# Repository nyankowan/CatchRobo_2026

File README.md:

# CatchRobo_2026
キャチロボ2026で使用する回路データおよび複数マイコンのプログラムを一括管理するリポジトリ.
Team: OBT

## Directory structure
```text
CatchRobo_2026/
├── common/                     ESP32/STM32が共有するプラットフォーム非依存コード
│   ├── arm/
│   │   └── アームの物理パラメータ・ホーミング関連定数・出場チーム(ROBOT_TEAM)
│   │
│   ├── can_protocol/
│   │   └── CAN IDとデータフォーマットの対応定義
│   │
│   └── coordinate/
│       └── 直交座標・極座標変換
│
├── ESP32/
│   └── controller/
│       └── Main Controller(プロコン入力の受信とCANによる各STM32への指令)
│
├── STM32/
│   ├── common/
│   │   └── can/
│   │       └── STM32 HAL CANを使ったCAN送信のラッパー
│   │
│   ├── robomas_controller/
│   │   └── 両アームのr軸・deg軸(Robomaster)制御．ホーミング処理の中枢
│   │
│   ├── lower_arm_servo/
│   │   └── 下アームのハンド(Left/Middle/Right/Expand)とShaftサーボ制御
│   │
│   ├── upper_arm_servo/
│   │   └── 上アームのShaft/Zサーボ制御
│   │
│   └── assemble_servo/
│       └── 整理機構のサーボ制御
│
└── Kicad/
    ├── ESP/
    │   └── ESP Main Controller基板
    ├── STM32F303K8_lower_arm_servo/
    │   └── サーボ制御基板(lower_arm_servo/upper_arm_servo/assemble_servoで共用)
    ├── STM32F446RE_robomas_controller/
    │   └── ロボマス制御基板
    ├── servo/
    │   └── サーボ用補助基板
    └── library/
        └── 共通シンボル・フットプリント
```

各ディレクトリの詳細は，それぞれのREADMEを参照．

| ディレクトリ | README |
| :--- | :--- |
| 共有コード | [common/README.md](common/README.md) |
| CAN通信仕様 | [common/can_protocol/README.md](common/can_protocol/README.md) |
| Main Controller | [ESP32/controller/README.md](ESP32/controller/README.md) |
| STM32全体 | [STM32/README.md](STM32/README.md) |
| 部品リスト | [Kicad/README.md](Kicad/README.md) |

## Hardware

### Actuator
- Robomaster M3508
- DS3225 Servo

### Sensor
- リミットスイッチ(ホーミング用，robomas_controllerに接続)

### Communication
- CAN 1Mbps (ESP32 - STM32, STM32 - Robomaster)

CAN ID・データフォーマットの仕様は [common/can_protocol/README.md](common/can_protocol/README.md) を参照．

## System overview

```mermaid
graph LR
    Pad1[Gamepad1] <-->|Bluetooth| ESP32[ESP32<br>中央制御]
    Pad2[Gamepad2] <-->|Bluetooth| ESP32

    ESP32 --- CAN[CAN BUS]

    CAN --- STM1[STM32 #1<br>robomas_controller]
    CAN --- STM2[STM32 #2<br>lower_arm_servo]
    CAN --- STM3[STM32 #3<br>upper_arm_servo]
    CAN --- STM4[STM32 #4<br>assemble_servo]

    STM1 <-->|CAN| Motor[Robomaster Motor<br>M3508]
    Limit[リミットスイッチ] -->|GPIO| STM1
    STM2 -->|PWM| Servo1[DS3225<br>Left/Middle/Right/Expand/Shaft]
    STM3 -->|PWM| Servo2[DS3225<br>Shaft/Z]
    STM4 -->|PWM| Servo3[DS3225<br>Assemble]
```

## Development environment

### ESP32

#### Hardware
- ESP32-DevKitC-32E

#### Software
- ESP-IDF v5.5.4
- VS Code + ESP-IDF Extension

### STM32

#### Hardware
- STM32 NUCLEO-F303K8
- STM32 NUCLEO-F446RE

#### Software
- STM32CubeMX
- CMake
- VS Code + STM32CubeIDE Extension

### KiCad

#### Software
- KiCad 10.0

## Build

### ESP32

#### Setup
[ESP-IDF環境構築手順（Windows）](https://app.notion.com/p/Windows-36e23f78736380f7b838e187b781a125?v=2cd23f78736380928f93000c8fceebd6&source=copy_link)

[ESP-IDF環境構築手順（Linux）](https://app.notion.com/p/L-32323f7873638072bacfeb84175d09c4?v=2cd23f78736380928f93000c8fceebd6&source=copy_link)

#### Build
```bash
idf.py build
```
#### Flash
```bash
idf.py flash
```

### STM32

#### Setup
[Qiita: STM32の開発をVSCodeで行う](https://qiita.com/tanutanup/items/d680c92f5168fc3f0182) [@tanutanup(tanutanu p)様](https://qiita.com/tanutanup)

#### Build
各プロジェクト(`STM32/lower_arm_servo`, `STM32/upper_arm_servo`, `STM32/robomas_controller`, `STM32/assemble_servo`)のディレクトリで実行する．
```bash
cmake --preset Release
cmake --build --preset Release
```

## 出場チーム(ROBOT_TEAM)の設定

赤/青チームはフィールドが鏡合わせで，整理機構を左右逆側に取り付けるため，DEG軸のホーミング原点やShaftサーボの回転方向をチームごとに切り替える必要がある．

出場チームは `common/arm/inc/arm.h` の `ROBOT_TEAM`(`ROBOT_TEAM_RED` / `ROBOT_TEAM_BLUE`)としてビルド時の定数で持たせている．緊急停止スイッチでESP32/STM32が再起動しても値を保持する必要があるため，実行時に切り替える方式にはしていない．

**出場チームに応じて`arm.h`のこの値を書き換えた後は，`arm.h`を使う全ファームウェア(ESP32 Main Controller，STM32の`robomas_controller` / `lower_arm_servo` / `upper_arm_servo`)を必ずビルド・書き込みし直すこと．** 値がずれると，DEG軸のホーミングで検出するリミットスイッチと回転方向が基板間で食い違い，可動域の反対側の固定端に衝突する恐れがある．

詳細は [STM32/robomas_controller/README.md](STM32/robomas_controller/README.md) を参照．

## CI

`.github/workflows/` でpush/pull request時に全ファームウェアのビルドを確認している．

| Workflow | 内容 |
| :--- | :--- |
| `esp32-build.yml` | `ESP32/controller` をESP-IDF v5.5.4でビルド |
| `stm32-build.yml` | STM32の4プロジェクトを`cmake --preset Release`でビルド |

ESP-IDFのバージョンとSTM32のツールチェーンは，上記「Development environment」およびDev Containerの設定と揃えること．

## Dev Container (Docker)

ESP-IDF拡張とSTM32系拡張は同じVS Codeウィンドウで有効になっていると干渉するため，用途別にDev Container(Docker)を分けている．必要な拡張機能だけがコンテナ内にインストールされるので，都度手動で拡張をオン/オフする必要がない．

| フォルダを開く | 使うコンテナ | 有効になる拡張 |
| :--- | :--- | :--- |
| `ESP32/controller` | `ESP32/controller/.devcontainer` | ESP-IDF |
| `STM32` | `STM32/.devcontainer` | clangd, CMake Tools, Cortex-Debug |

使い方: 対象のフォルダ(リポジトリ全体ではなく上表のフォルダ)を`File > Open Folder...`で開き，コマンドパレットから`Dev Containers: Reopen in Container`を実行する．どちらのコンテナも各プロジェクトが参照する`common/`(リポジトリ直下)を含むリポジトリ全体をマウントしたうえで，開いたフォルダをエディタ上のワークスペースフォルダとして表示する．

`STM32/.devcontainer`は`lower_arm_servo`/`upper_arm_servo`/`robomas_controller`/`assemble_servo`の4プロジェクト共通で，どのプロジェクトも同じコンテナ内でビルドできる(各プロジェクトのディレクトリに`cd`して上記の`cmake --preset`コマンドを実行)．

`ESP32/controller/.devcontainer`はコンテナ作成時に`components/procon`が依存するBluepad32/BTstack(`~/.espressif/bluepad32`)を自動で取得する(`esp32-build.yml`と同じ手順)．取得結果はDockerボリュームにキャッシュされるため，コンテナを再作成しても毎回cloneし直すことはない．

ST-Link/シリアルポート経由でのフラッシュ・デバッグにはUSBデバイスをコンテナに渡す必要があり，Linuxホスト以外(Windows/macOS)では別途パススルー設定が必要な場合がある．

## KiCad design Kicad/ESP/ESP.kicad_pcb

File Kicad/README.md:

# Kicad

キャチロボ2026で使用する回路データ(KiCad 10.0)と，その部品リスト．

## Directory structure

```text
Kicad/
├── ESP/
│   └── ESP Main Controller基板(ESP32-DevKitC-32E)
│
├── STM32F303K8_lower_arm_servo/
│   └── サーボ制御基板(lower_arm_servo/upper_arm_servo/assemble_servoで共用)
│
├── STM32F446RE_robomas_controller/
│   └── ロボマス制御基板(NUCLEO-F446RE)
│
├── servo/
│   └── サーボ用補助基板
│
└── library/
    └── 共通シンボル・フットプリント
```

各基板に対応するファームウェアは [STM32/README.md](../STM32/README.md) および [ESP32/controller/README.md](../ESP32/controller/README.md) を参照．

## 部品リスト

このディレクトリにあるキャチロボ2026に向けて作った回路データのほかにも，
岡ロボで使われるCANトランシーバー回路も使用している．

### 回路基板実装部品
#### マイコン基板
- lower_arm_servo基板×3（上側アームと整理機構の制御基板に流用）     
以下一つあたりの部品
    - nucleo-f303k8
    - 3φLED×1
    - 470Ω抵抗×1
    - 5ピンソケット×1
    - 6ピンソケット×1
    - 15pin socket×2

- robomas_controller基板×1
    - nucleo-f446re
    - 19*2ピンソケット×2
    - hirose 2pin(DF1EC-2P-2.5DSA(35))×7
    - 5ピンソケット×2
    - 300Ω抵抗×1
    - φ3LED×1

- ESP Main controller基板×1
    - ESP32-DevKitC-32E
    - 19ピンソケット×2
    - 2ピンソケット×2
    - 5ピンソケット×1
    - φ3LED×7
    - 470Ω抵抗×7

#### 電源基板(N先輩制作)
- catchrobo_2026電源回路×1
    - リレー(942H-2C-24DS)×1
    - ヒューズ×3
    - 470μF×3
    - xt30オス×5
    - xt30メス×4
    - φ5LED×3
    - {1200, 330}Ω抵抗×3
- catchrobo_2026分電回路×2
    - 470μF×1
    - φ5LED×1
    - {1200, 330}Ω抵抗×1
    - xt30メス×4
    - xt30オス×1

#### 補助基板
- servo基板×3   
一つあたりの部品
    - 基板取付用XT30オス(XT30PW-M)×1
    - 1kΩ抵抗×1
    - 220Ω抵抗×5
    - φ3LED×1
    - 1000μF(50PX1000MEFC12.5X25)×1
    - 0.1μF(積層セラミックコンデンサー 0.1μF100V X7R 5mmピッチ)
    - 折れ6pin hirose (DF1E-6P-2.5DS(35))×1
    - 3ピンソケット×5（ヘッダでも可）

- canトランシーバ基板ver1.b×2
- canトランシーバ基板ver1.0×1
- canトランシーバ基板ver1.0 終端抵抗なし×3

- 6.6V -> 5V DCDCコンバータ×1
    - xt30オス×1
    - xt30メス×1

### コード類
#### 電源線
- 電源供給用micro-B×3（2m級×2）
- 電源供給用micro-B×1 （もしくは 2pin オスxt30メス×1）
- 電源供給用mini-B×1　（もしくは 2pin オスxt30メス×1）
- ロボマス電源延長用 xt30 オスメス ×4（15cm程度）
- xt30延長ケーブル×∞

#### 信号線
- リミットスイッチ 2pin hirose オス×6（2m級）
- マイコン間canbus接続用2pin hirose オスオス×4（2m級）
- サーボ電源供給用 xt30オスメス×3（2m級）
- ロボマスcan延長用 2pin hirose オスメス×4（15cm程度）
- canトランシーバ接続用6pinオスメスコネクタ×1（1pin NC）

#### その他
- サーボ延長用 3pin オスメス×5

### 非常停止ボタン　動作ランプなど
- プッシュロック・ターンリセットスイッチ×1
- φ20以上緑LED×1(HWシリーズ パイロットライトΦ22(突形 LED))
- 22VLipo×3
    - xt60オス - xt30メス変換ケーブル×1
- 6.6VLipo×1(並列につなぐ場合×2)
    - xt60オス - xt30メス変換ケーブル×1

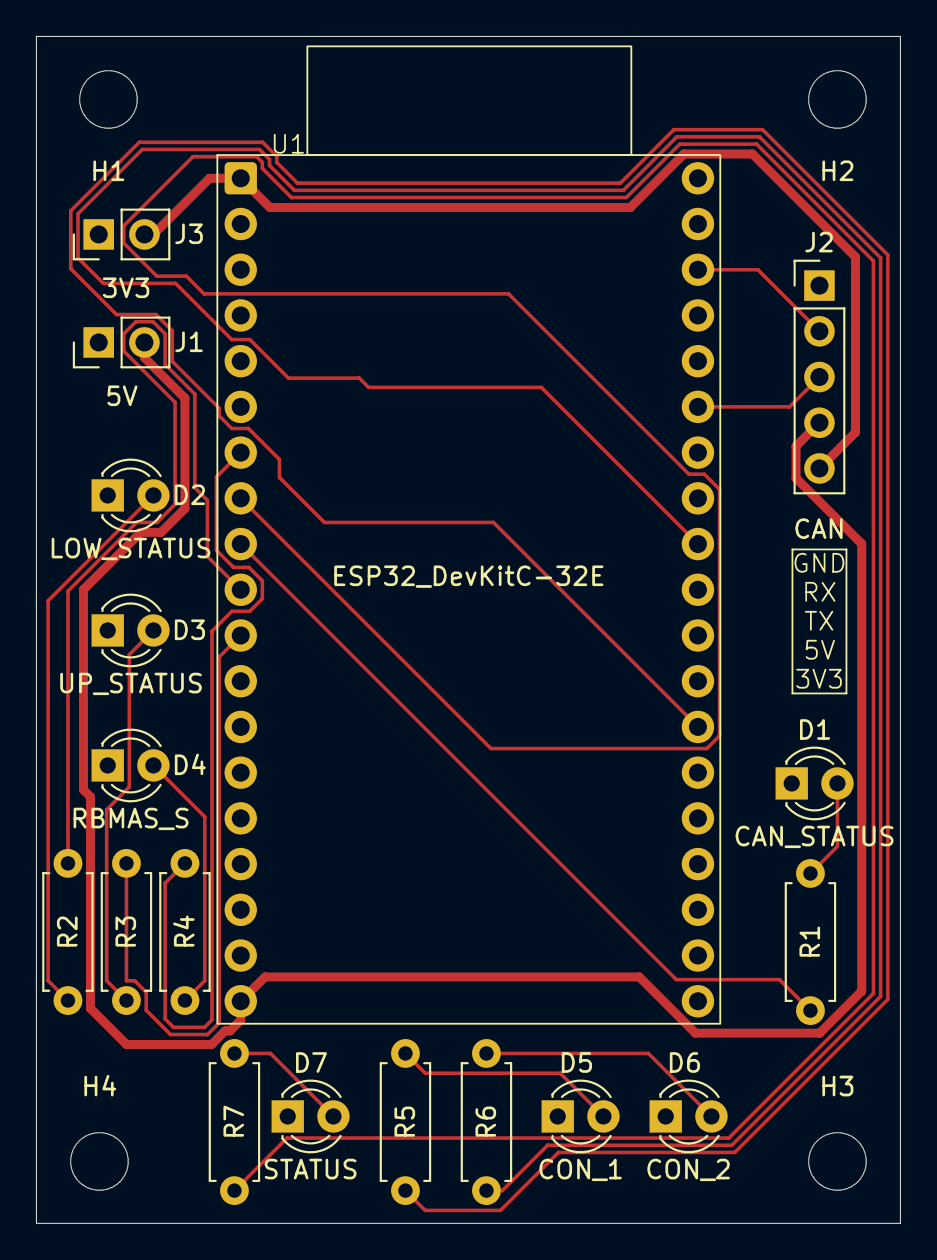
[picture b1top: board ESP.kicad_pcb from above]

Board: 2 copper layers, 48.0 x 65.9 mm, 22 parts (0 on the bottom side), 19 nets.

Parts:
D1: CAN_STATUS; LED_D3.0mm
D2: LOW_STATUS; LED_D3.0mm
D3: UP_STATUS; LED_D3.0mm
D4: RBMAS_S; LED_D3.0mm
D5: CON_1; LED_D3.0mm
D6: CON_2; LED_D3.0mm
D7: STATUS; LED_D3.0mm
H1, H2, H3, H4: MountingHole; MountingHole_3.2mm_M3
J1: 5V; PinHeader_1x02_P2.54mm_Vertical
J2: CAN; PinHeader_1x05_P2.54mm_Vertical
J3: 3V3; PinHeader_1x02_P2.54mm_Vertical
R1, R2, R3, R4, R5, R6, R7: 300R; R_Axial_DIN0207_L6.3mm_D2.5mm_P7.62mm_Horizontal
U1: ESP32_DevKitC-32E; ESP32_DevKitC_32E

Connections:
+3.3V: J2.5, J3.2, U1.1 (3V3)
+5V: J1.2, J2.4, U1.19 (5V)
/CAN_RX: J2.2, U1.22 (GPIO22)
/CAN_STATUS_LED_GPIO: R1.1, U1.9 (GPIO25)
/CAN_TX: J2.3, U1.25 (GPIO21)
/CONTROLLER_1_LED_GPIO: R5.1, U1.32 (GPIO4)
/CONTROLLER_2_LED_GPIO: R6.1, U1.28 (GPIO18)
/LOWER_ARM_STATUS_LED_GPIO: R2.1, U1.10 (GPIO26)
/ROBOMAS_CONTROLLER_STATUS_LED_GPIO: R4.1, U1.7 (GPIO32)
/STATUS_LED_GPIO: R7.1, U1.8 (GPIO33)
/UPPER_ARM_STATUS_LED_GPIO: R3.1, U1.11 (GPIO27)
GND: D1.1 (K), D2.1 (K), D3.1 (K), D4.1 (K), D5.1 (K), D6.1 (K), D7.1 (K), J1.1, J2.1, J3.1, U1.14 (GND), U1.20 (GND), U1.26 (GND)
unnamed: D1.2 (A), R1.2
unnamed: D2.2 (A), R2.2
unnamed: D3.2 (A), R3.2
unnamed: D4.2 (A), R4.2
unnamed: D5.2 (A), R5.2
unnamed: D6.2 (A), R6.2
unnamed: D7.2 (A), R7.2

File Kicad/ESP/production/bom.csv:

Designator,Footprint,Quantity,Value,LCSC Part #
D1,LED_D3.0mm,1,CAN_STATUS,
D2,LED_D3.0mm,1,LOW_STATUS,
D3,LED_D3.0mm,1,UP_STATUS,
D4,LED_D3.0mm,1,RBMAS_S,
D5,LED_D3.0mm,1,CON_1,
D6,LED_D3.0mm,1,CON_2,
D7,LED_D3.0mm,1,STATUS,
J1,PinHeader_1x02_P2.54mm_Vertical,1,5V,
J2,PinHeader_1x05_P2.54mm_Vertical,1,CAN,
J3,PinHeader_1x02_P2.54mm_Vertical,1,3V3,
"R1, R2, R3, R4, R5, R6, R7",R_Axial_DIN0207_L6.3mm_D2.5mm_P7.62mm_Horizontal,7,300R,
U1,ESP32_DevKitC_32E,1,ESP32_DevKitC-32E,

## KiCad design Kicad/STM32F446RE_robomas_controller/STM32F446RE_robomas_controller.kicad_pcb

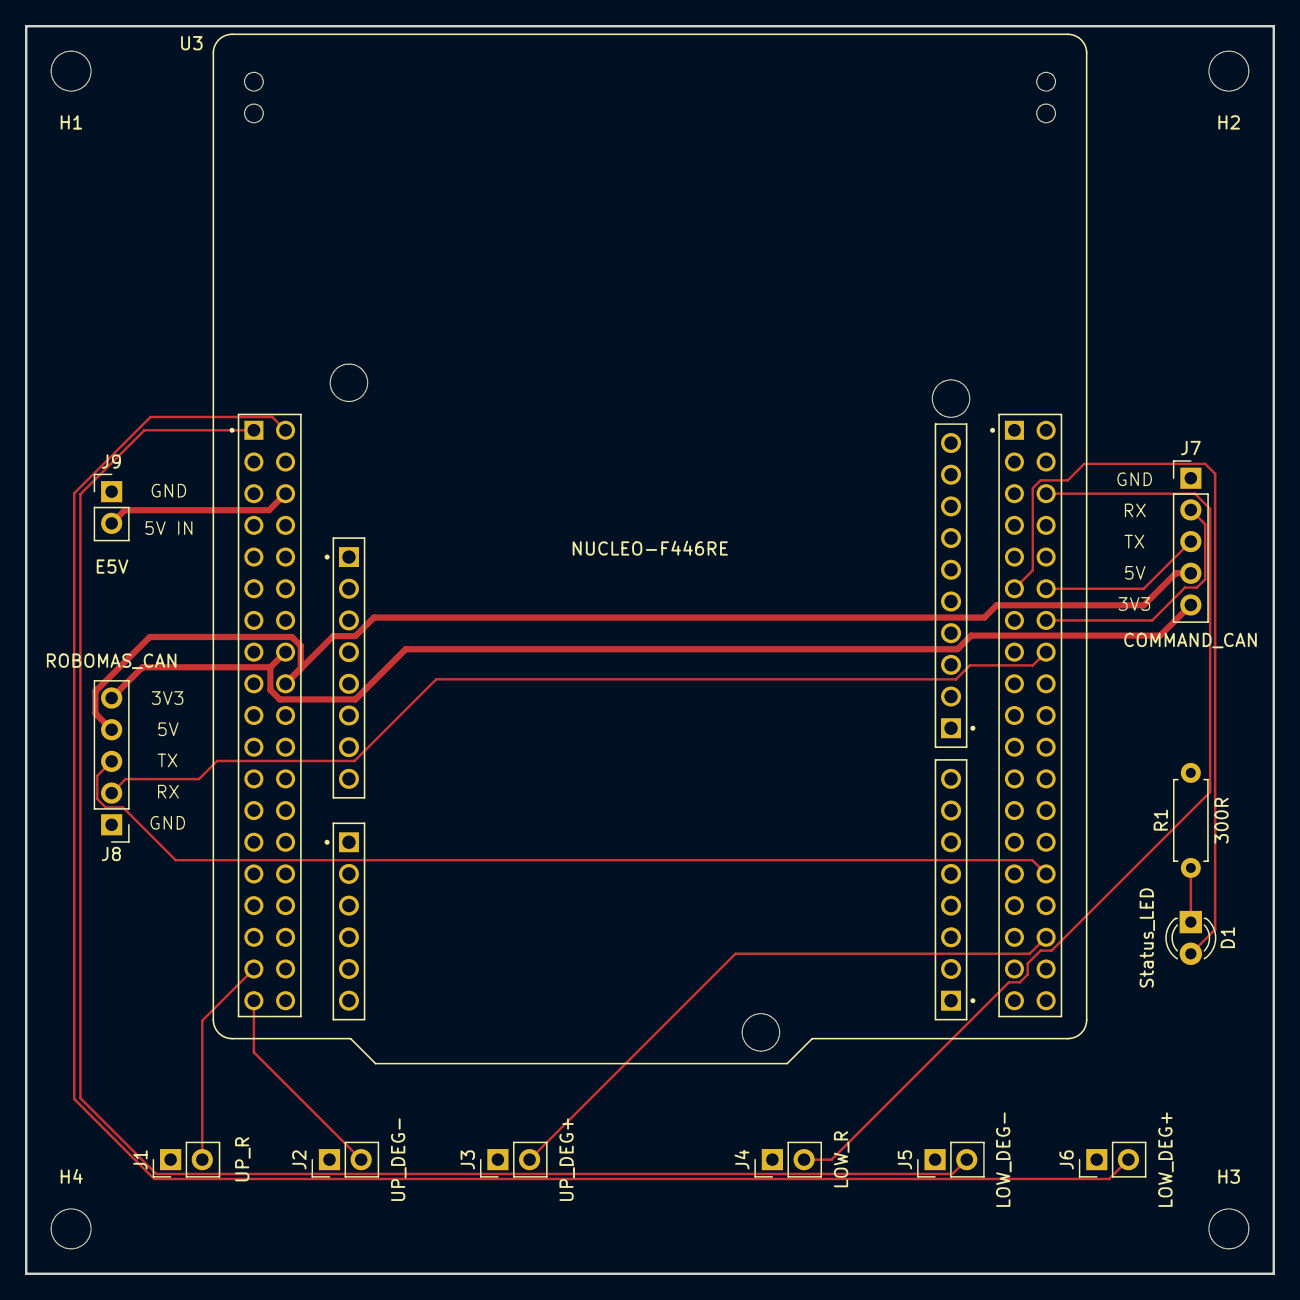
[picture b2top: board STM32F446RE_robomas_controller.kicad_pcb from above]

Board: 2 copper layers, 100.0 x 100.0 mm, 16 parts (0 on the bottom side), 16 nets.

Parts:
D1: Status_LED; LED_D3.0mm
H1, H2, H3, H4: MountingHole; MountingHole_3.2mm_M3
J1: UP_R; PinHeader_1x02_P2.54mm_Vertical
J2: UP_DEG-; PinHeader_1x02_P2.54mm_Vertical
J3: UP_DEG+; PinHeader_1x02_P2.54mm_Vertical
J4: LOW_R; PinHeader_1x02_P2.54mm_Vertical
J5: LOW_DEG-; PinHeader_1x02_P2.54mm_Vertical
J6: LOW_DEG+; PinHeader_1x02_P2.54mm_Vertical
J7: COMMAND_CAN; PinHeader_1x05_P2.54mm_Vertical
J8: ROBOMAS_CAN; PinHeader_1x05_P2.54mm_Vertical
J9: E5V; PinHeader_1x02_P2.54mm_Vertical
R1: 300R; R_Axial_DIN0207_L6.3mm_D2.5mm_P7.62mm_Horizontal
U3: NUCLEO-F446RE; MODULE_NUCLEO-F446RE_CN11_CN12_clearance

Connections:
+3.3V: J7.5, J8.5, U3.CN7_16 (CN7_+3V3)
+5V: J7.4, J8.4, U3.CN7_18 (CN7_+5V)
/COMMAND_CAN_RX: J7.2, U3.CN10_14 (PA11)
/COMMAND_CAN_TX: J7.3, U3.CN10_12 (PA12)
/E5V: J9.2, U3.CN7_6 (E5V)
/LOWER_ARM_DEG_OVER_LIMIT: J6.2, U3.CN7_2 (PC11)
/LOWER_ARM_DEG_UNDER_LIMIT: J5.2, U3.CN7_1 (PC10)
/LOWER_ARM_R_LIMIT: J4.2, U3.CN10_6 (PC5)
/ROBOMAS_CAN_RX: J8.2, U3.CN10_16 (PB12)
/ROBOMAS_CAN_TX: J8.3, U3.CN10_30 (PB13)
/Status_LED: D1.2 (A), U3.CN10_11 (PA5)
/UPPER_ARM_DEG_OVER_LIMIT: J3.2, U3.CN10_34 (PC4)
/UPPER_ARM_DEG_UNDER_LIMIT: J2.2, U3.CN7_37 (PC3)
/UPPER_ARM_R_LIMIT: J1.2, U3.CN7_35 (PC2)
GND: J1.1, J2.1, J3.1, J4.1, J5.1, J6.1, J7.1, J8.1, J9.1, R1.2, U3.CN7_8 (CN7_GND), U3.CN7_19 (CN7_GND__1), U3.CN7_20 (CN7_GND__2), U3.CN7_22 (CN7_GND__3), U3.CN10_9 (CN10_GND), U3.CN10_20 (CN10_GND__1), U3.CN10_32 (AGND)
unnamed: D1.1 (K), R1.1

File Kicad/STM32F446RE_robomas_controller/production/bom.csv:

Designator,Footprint,Quantity,Value,LCSC Part #
D1,LED_D3.0mm,1,Status_LED,
J1,PinHeader_1x02_P2.54mm_Vertical,1,UP_R,
J2,PinHeader_1x02_P2.54mm_Vertical,1,UP_DEG-,
J3,PinHeader_1x02_P2.54mm_Vertical,1,UP_DEG+,
J4,PinHeader_1x02_P2.54mm_Vertical,1,LOW_R,
J5,PinHeader_1x02_P2.54mm_Vertical,1,LOW_DEG-,
J6,PinHeader_1x02_P2.54mm_Vertical,1,LOW_DEG+,
J7,PinHeader_1x05_P2.54mm_Vertical,1,COMMAND_CAN,
J8,PinHeader_1x05_P2.54mm_Vertical,1,ROBOMAS_CAN,
J9,PinHeader_1x02_P2.54mm_Vertical,1,E5V,
R1,R_Axial_DIN0207_L6.3mm_D2.5mm_P7.62mm_Horizontal,1,300R,
U3,MODULE_NUCLEO-F446RE_CN11_CN12_clearance,1,NUCLEO-F446RE,

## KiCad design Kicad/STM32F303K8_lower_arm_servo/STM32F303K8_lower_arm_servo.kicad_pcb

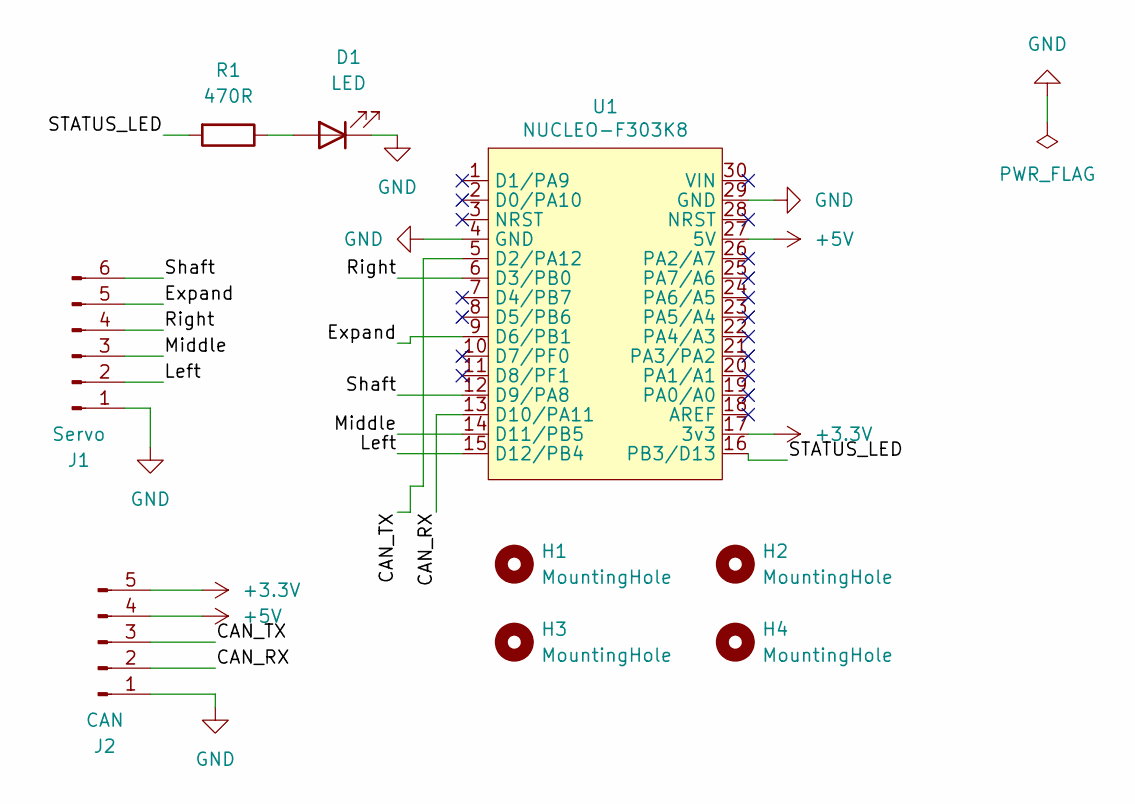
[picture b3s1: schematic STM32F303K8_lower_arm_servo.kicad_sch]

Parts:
D1: LED; LED_D3.0mm
H1, H2, H3, H4: MountingHole; MountingHole_3.2mm_M3
J1: Servo; PinHeader_1x06_P2.54mm_Vertical
J2: CAN; PinHeader_1x05_P2.54mm_Vertical
R1: 470R; R_Axial_DIN0207_L6.3mm_D2.5mm_P7.62mm_Horizontal
U1: NUCLEO-F303K8

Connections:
+3.3V: J2.5, U1.17 (3v3)
+5V: J2.4, U1.27 (5V)
/CAN_RX: J2.2, U1.13 (D10/PA11)
/CAN_TX: J2.3, U1.5 (D2/PA12)
/Expand: J1.5, U1.9 (D6/PB1)
/Left: J1.2, U1.15 (D12/PB4)
/Middle: J1.3, U1.14 (D11/PB5)
/Right: J1.4, U1.6 (D3/PB0)
/STATUS_LED: R1.2, U1.16 (PB3/D13)
/Shaft: J1.6, U1.12 (D9/PA8)
GND: D1.1 (K), J1.1, J2.1, U1.4 (GND), U1.29 (GND)
unnamed: D1.2 (A), R1.1

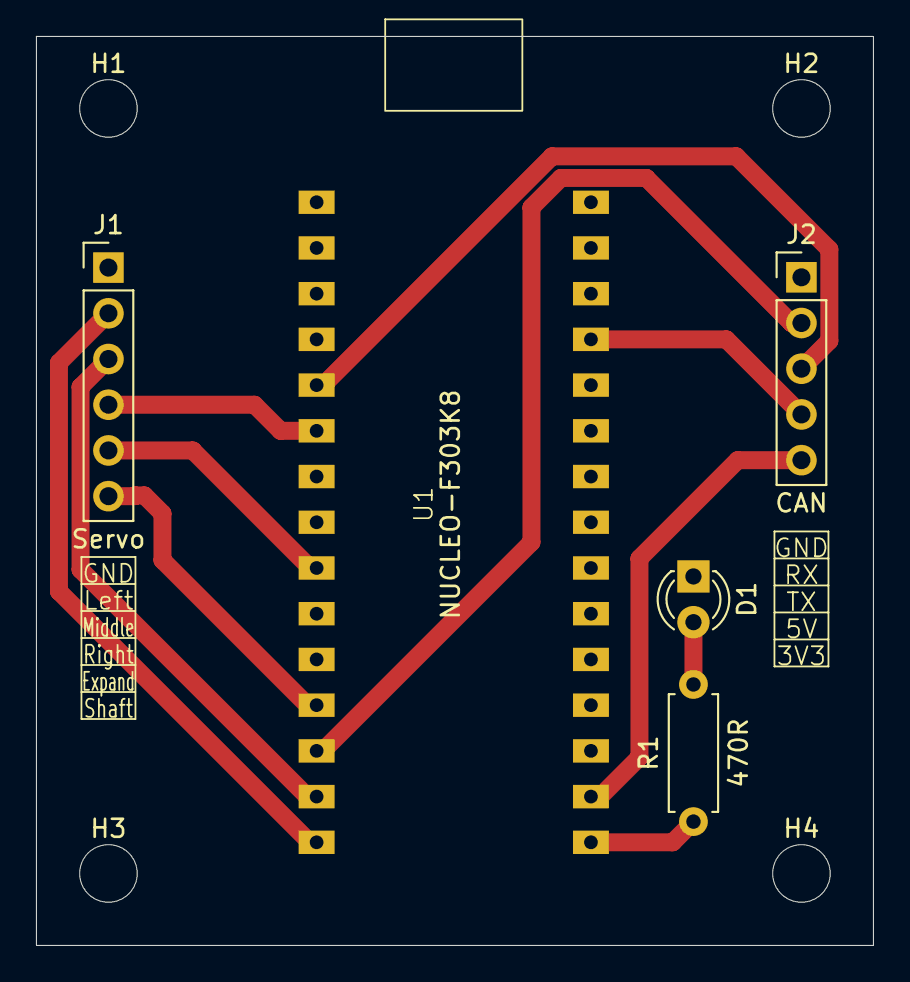
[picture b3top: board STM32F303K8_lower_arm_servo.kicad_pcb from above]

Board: 2 copper layers, 46.5 x 50.5 mm, 9 parts (0 on the bottom side), 12 nets.

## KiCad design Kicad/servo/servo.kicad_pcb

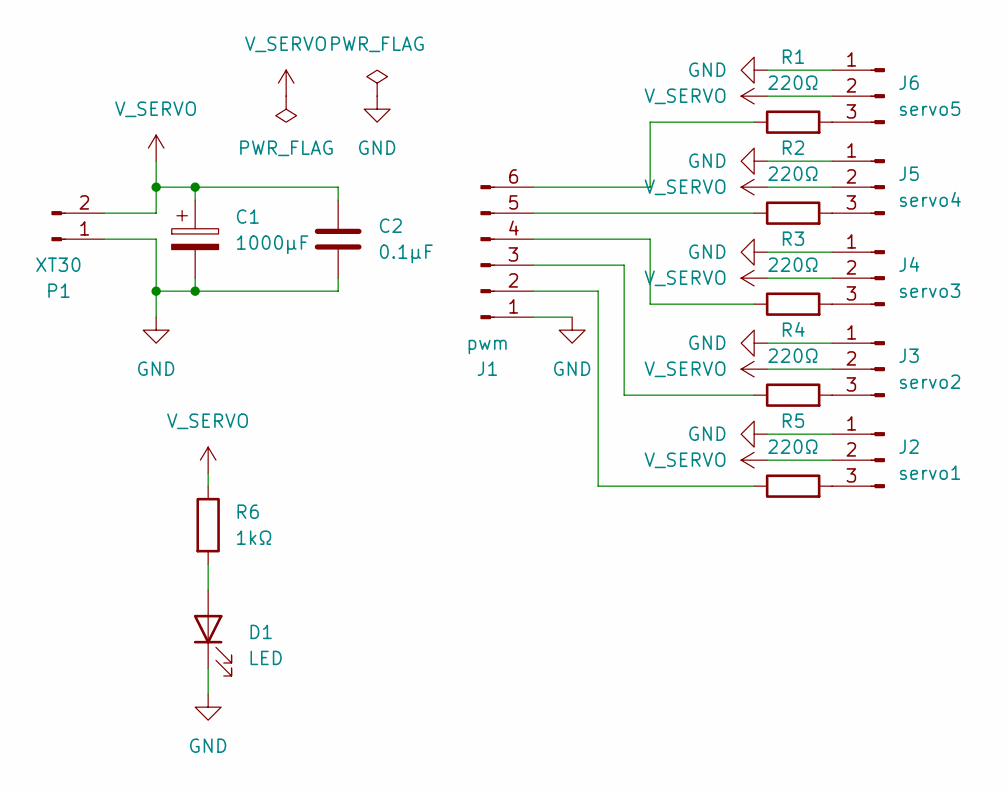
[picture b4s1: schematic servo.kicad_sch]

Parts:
C1: 1000μF; CP_Radial_D12.5mm_P5.00mm
C2: 0.1μF; C_Disc_D5.0mm_W2.5mm_P5.00mm
D1: LED; LED_D3.0mm
J1: pwm; PinHeader_1x06_P2.54mm_Vertical
J2: servo1; PinHeader_1x03_P2.54mm_Vertical
J3: servo2; PinHeader_1x03_P2.54mm_Vertical
J4: servo3; PinHeader_1x03_P2.54mm_Vertical
J5: servo4; PinHeader_1x03_P2.54mm_Vertical
J6: servo5; PinHeader_1x03_P2.54mm_Vertical
P1: XT30; AMASS_XT30PW-M_1x02_P2.50mm_Horizontal
R1, R2, R3, R4, R5: 220Ω; R_Axial_DIN0207_L6.3mm_D2.5mm_P7.62mm_Horizontal
R6: 1kΩ; R_Axial_DIN0207_L6.3mm_D2.5mm_P7.62mm_Horizontal

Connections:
GND: C1.2, C2.2, D1.1 (K), J1.1, J2.1, J3.1, J4.1, J5.1, J6.1, P1.1
unnamed: D1.2 (A), R6.2
unnamed: J1.2, R5.1
unnamed: J1.3, R4.1
unnamed: J1.4, R3.1
unnamed: J1.5, R2.1
unnamed: J1.6, R1.1
unnamed: J2.3, R5.2
unnamed: J3.3, R4.2
unnamed: J4.3, R3.2
unnamed: J5.3, R2.2
unnamed: J6.3, R1.2
V_SERVO: C1.1, C2.1, J2.2, J3.2, J4.2, J5.2, J6.2, P1.2, R6.1

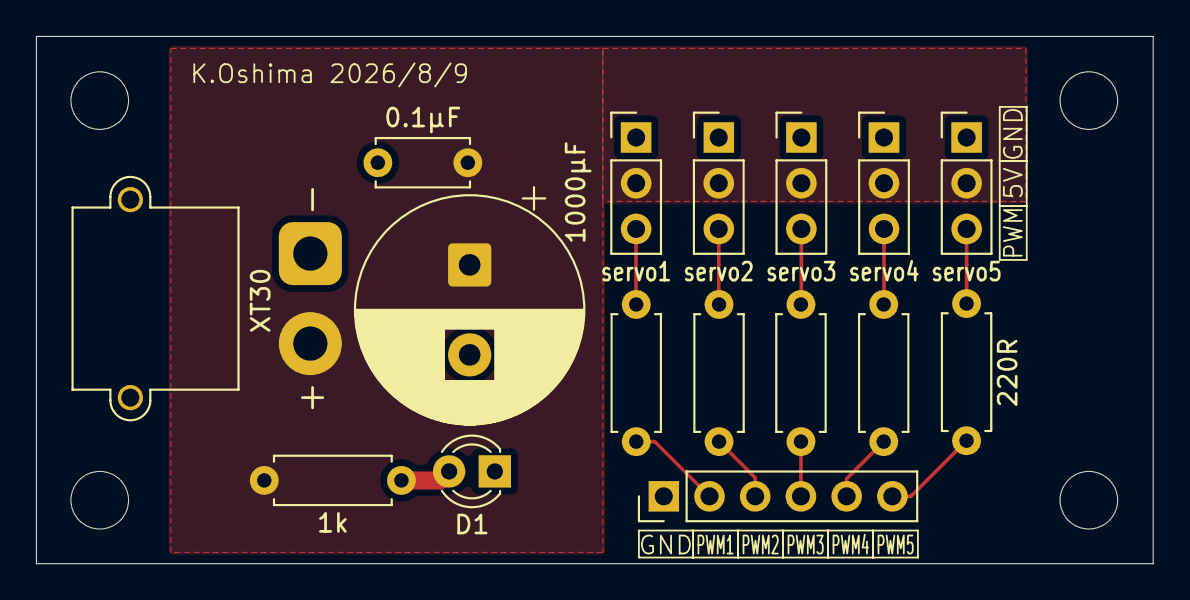
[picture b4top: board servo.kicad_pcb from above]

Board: 2 copper layers, 62.0 x 29.3 mm, 16 parts (0 on the bottom side), 13 nets.

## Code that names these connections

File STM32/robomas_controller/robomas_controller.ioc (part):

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Mcu.Name=STM32F446R(C-E)Tx
Mcu.Package=LQFP64
Mcu.UserName=STM32F446RETx
PA11.GPIOParameters=GPIO_Label
PA11.GPIO_Label=COMMAND_CAN_RX
PA11.Mode=CAN_Activate
PA11.Signal=CAN1_RX
PA12.GPIOParameters=GPIO_Label
PA12.GPIO_Label=COMMAND_CAN_TX
PA12.Mode=CAN_Activate
PA12.Signal=CAN1_TX
PA13.GPIOParameters=GPIO_Label
PA13.GPIO_Label=TMS
PA13.Mode=Serial_Wire
PA13.Signal=SYS_JTMS-SWDIO
PA14.GPIOParameters=GPIO_Label
PA14.GPIO_Label=TCK
PA14.Mode=Serial_Wire
PA14.Signal=SYS_JTCK-SWCLK
PA2.GPIOParameters=GPIO_Label
PA2.GPIO_Label=USART_TX
PA2.Mode=Asynchronous
PA2.Signal=USART2_TX
PA3.GPIOParameters=GPIO_Label
PA3.GPIO_Label=USART_RX
PA3.Mode=Asynchronous
PA3.Signal=USART2_RX
PA5.GPIOParameters=GPIO_Label
PA5.GPIO_Label=Status_LED
PA5.Signal=GPIO_Output
PB12.GPIOParameters=GPIO_Label
PB12.GPIO_Label=ROBOMAS_CAN_RX
PB12.Mode=CAN_Activate
PB12.Signal=CAN2_RX
PB13.GPIOParameters=GPIO_Label
PB13.GPIO_Label=ROBOMAS_CAN_TX
PB13.Mode=CAN_Activate
PB13.Signal=CAN2_TX
PB3.GPIOParameters=GPIO_Label
PB3.GPIO_Label=SWO
PB3.Signal=SYS_JTDO-SWO
PC10.GPIOParameters=GPIO_PuPd,GPIO_Label
PC10.GPIO_Label=LOWER_ARM_DEG_UNDER_LIMIT
PC10.GPIO_PuPd=GPIO_PULLUP
PC10.Signal=GPIO_Input
PC11.GPIOParameters=GPIO_PuPd,GPIO_Label
PC11.GPIO_Label=LOWER_ARM_DEG_OVER_LIMIT
PC11.GPIO_PuPd=GPIO_PULLUP
PC11.Signal=GPIO_Input
PC13.GPIOParameters=GPIO_Label,GPIO_ModeDefaultEXTI
PC13.GPIO_Label=B1 [Blue PushButton]
PC13.GPIO_ModeDefaultEXTI=GPIO_MODE_IT_FALLING
PC13.Signal=GPXTI13
PC14-OSC32_IN.Mode=LSE-External-Oscillator
PC14-OSC32_IN.Signal=RCC_OSC32_IN
PC15-OSC32_OUT.Mode=LSE-External-Oscillator
PC15-OSC32_OUT.Signal=RCC_OSC32_OUT
PC2.GPIOParameters=GPIO_PuPd,GPIO_Label
PC2.GPIO_Label=UPPER_ARM_R_LIMIT
PC2.GPIO_PuPd=GPIO_PULLUP
PC2.Signal=GPIO_Input
PC3.GPIOParameters=GPIO_PuPd,GPIO_Label
PC3.GPIO_Label=UPPER_ARM_DEG_UNDER_LIMIT
PC3.GPIO_PuPd=GPIO_PULLUP
PC3.Signal=GPIO_Input
PC4.GPIOParameters=GPIO_PuPd,GPIO_Label
PC4.GPIO_Label=UPPER_ARM_DEG_OVER_LIMIT
PC4.GPIO_PuPd=GPIO_PULLUP
PC4.Signal=GPIO_Input
PC5.GPIOParameters=GPIO_PuPd,GPIO_Label
PC5.GPIO_Label=LOWER_ARM_R_LIMIT
PC5.GPIO_PuPd=GPIO_PULLUP
PC5.Signal=GPIO_Input
PH0-OSC_IN.Mode=HSE-External-Oscillator
PH0-OSC_IN.Signal=RCC_OSC_IN
PH1-OSC_OUT.Mode=HSE-External-Oscillator
PH1-OSC_OUT.Signal=RCC_OSC_OUT
RCC.HSE_VALUE=8000000
RCC.SYSCLKFreq_VALUE=60000000
RCC.SYSCLKSource=RCC_SYSCLKSOURCE_PLLCLK
board=NUCLEO-F446RE
boardIOC=true

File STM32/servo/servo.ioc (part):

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Mcu.Name=STM32F303K(6-8)Tx
Mcu.Package=LQFP32
Mcu.UserName=STM32F303K8Tx
PA11.GPIOParameters=GPIO_Label
PA11.GPIO_Label=CAN_RX
PA11.Mode=CAN_Activate
PA11.Signal=CAN_RX
PA12.GPIOParameters=GPIO_Label
PA12.GPIO_Label=CAN_TX
PA12.Mode=CAN_Activate
PA12.Signal=CAN_TX
PA13.GPIOParameters=GPIO_Label
PA13.GPIO_Label=SWDIO
PA13.Mode=Serial_Wire
PA13.Signal=SYS_JTMS-SWDIO
PA14.GPIOParameters=GPIO_Label
PA14.GPIO_Label=SWCLK
PA14.Mode=Serial_Wire
PA14.Signal=SYS_JTCK-SWCLK
PA15.GPIOParameters=GPIO_Label
PA15.GPIO_Label=VCP_RX
PA15.Mode=Asynchronous
PA15.Signal=USART2_RX
PA2.GPIOParameters=GPIO_Label
PA2.GPIO_Label=VCP_TX
PA2.Mode=Asynchronous
PA2.Signal=USART2_TX
PA8.GPIOParameters=GPIO_Label
PA8.GPIO_Label=Shaft
PA8.Signal=S_TIM1_CH1
PB0.GPIOParameters=GPIO_Label
PB0.GPIO_Label=Right
PB0.Signal=S_TIM3_CH3
PB1.GPIOParameters=GPIO_Label
PB1.GPIO_Label=Expand
PB1.Signal=S_TIM3_CH4
PB3.GPIOParameters=GPIO_Label
PB3.GPIO_Label=STATUS_LED
PB3.Signal=GPIO_Output
PB4.GPIOParameters=GPIO_Label
PB4.GPIO_Label=Left
PB4.Signal=S_TIM3_CH1
PB5.GPIOParameters=GPIO_Label
PB5.GPIO_Label=Middle
PB5.Signal=S_TIM3_CH2
PF0\ /\ OSC_IN.GPIOParameters=GPIO_Label
PF0\ /\ OSC_IN.GPIO_Label=MCO
PF0\ /\ OSC_IN.Mode=HSE-External-Clock-Source
PF0\ /\ OSC_IN.Signal=RCC_OSC_IN
RCC.HSEPLLFreq_Value=8000000
RCC.HSE_VALUE=8000000
RCC.SYSCLKFreq_VALUE=8000000
board=NUCLEO-F303K8
boardIOC=true

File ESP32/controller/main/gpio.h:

#ifndef GPIO_H
#define GPIO_H

#define CAN_TX_GPIO 21
#define CAN_RX_GPIO 22

#define CAN_STATUS_LED_GPIO                 25
#define LOWER_ARM_STATUS_LED_GPIO           26
#define UPPER_ARM_STATUS_LED_GPIO           27
#define ROBOMAS_CONTROLLER_STATUS_LED_GPIO  32
#define STATUS_LED_GPIO                     33
#define CONTROLLER_1_LED_GPIO                4
#define CONTROLLER_2_LED_GPIO               18

#endif // GPIO_H
